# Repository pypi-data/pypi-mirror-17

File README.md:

# PyPI code 17

This repo contains 40000 packages uploaded to PyPI between 
2016-08-28 20:14 and 2016-10-24 17:08.

The repo is 99% (39960/40000) complete.

Package contents can be found [in the code branch](https://github.com/pypi-data/pypi-mirror-17/tree/code/packages).

A browsable package list for all repositories [all packages here](https://pypi-data.github.io/website/repositories/pypi-mirror-17).

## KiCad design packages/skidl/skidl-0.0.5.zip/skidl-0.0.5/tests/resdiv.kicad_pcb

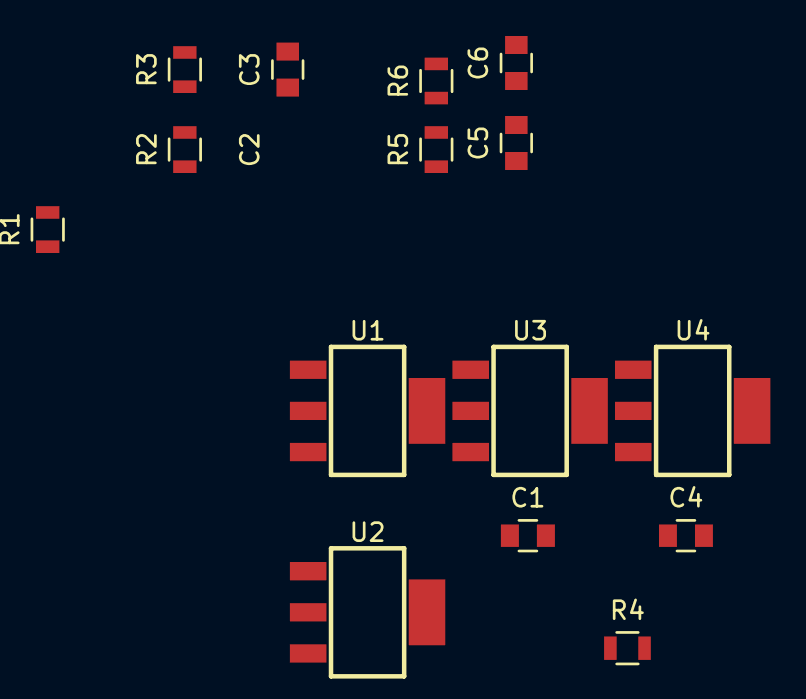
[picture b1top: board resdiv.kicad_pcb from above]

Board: 2 copper layers, 16 parts (0 on the bottom side), 4 nets, no tracks yet.

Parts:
C1, C4: C-NONPOL; C_0805
C2, C5: 1uF; C_0805
C3, C6: 2uF; C_0805
R1, R4: R; R_0805
R2, R5: 1K6; R_0805
R3, R6: 500K3; R_0805
U1, U2, U3, U4: NCV1117; SOT-223

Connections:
A: C2.1, R2.1, U1.3, U2.3
B: C2.2, C3.1, C5.1, R2.2, R3.1, R5.1, U1.2, U2.2, U3.3, U4.3
GND: C3.2, C6.2, R3.2, R6.2, U1.1, U2.1, U3.1, U4.1
unnamed: C5.2, C6.1, R5.2, R6.1, U3.2, U4.2

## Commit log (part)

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2023-08-06 Add package django-fobi/0.9.2/django-fobi-0.9.2.tar.gz
2023-08-06 Add package itchat/1.1.18/itchat-1.1.18-py2.py3-none-any.whl
2023-08-06 Add package ase/3.12.0/ase-3.12.0.tar.gz
2023-08-06 Add package klue-client-server/0.0.102/klue-client-server-0.0.102.tar.gz
2023-08-06 Add package nyaa-cli/0.0.1.dev10/nyaa-cli-0.0.1.dev10.tar.gz
2023-08-06 Add package learn2map/0.2.1/learn2map-0.2.1-py3-none-any.whl
2023-08-06 Add package log4mongo/1.6.0/log4mongo-1.6.0.tar.gz
2023-08-06 Add package zeep/0.20.0/zeep-0.20.0-py2.py3-none-any.whl
2023-08-06 Add package django-wordpress-api/0.1.11/django-wordpress-api-0.1.11.tar.gz
2023-08-06 Add package itchat/1.1.18/itchat-1.1.18.tar.gz
2023-08-06 Add package zeep/0.20.0/zeep-0.20.0.tar.gz
2023-08-06 Add package webm/0.10.0/webm-0.10.0.tar.gz
2023-08-06 Add package HRlo/0.7.2/HRlo-0.7.2.tar.gz
2023-08-06 Add package minicache/0.0.1/minicache-0.0.1.zip
2023-08-06 Add package silent-auction/0.1.3/silent-auction-0.1.3.tar.gz
2023-08-06 Add package invenio-search/1.0.0a8/invenio-search-1.0.0a8.tar.gz
2023-08-06 Add package CryDeer/0.2.3/CryDeer-0.2.3.tar.gz
2023-08-06 Add package uh/0.0.0/uh-0.0.0.tar.gz
2023-08-06 Add package mssqlcli/1.0.1b0/mssqlcli-1.0.1b0.tar.gz
2023-08-06 Add package coin/0.23/coin-0.23.tar.gz
2023-08-06 Add package podaacpy/1.5.0/podaacpy-1.5.0-py3.3.egg
2023-08-06 Add package aloe/0.1.11/aloe-0.1.11.tar.gz
2023-08-06 Add package pyboto3/1.3/pyboto3-1.3-py2.7.egg
2023-08-06 Add package podaacpy/1.5.0/podaacpy-1.5.0.tar.gz
2023-08-06 Add package phrasemachine/1.0.1/phrasemachine-1.0.1.tar.gz
2023-08-06 Add package mamonsu/2.1.3/mamonsu-2.1.3.tar.gz
2023-08-06 Add package wikitextparser/0.8.6.dev1/wikitextparser-0.8.6.dev1.tar.gz
2023-08-06 Add package grako/3.16.2/grako-3.16.2.zip
2023-08-06 Add package pyboto3/1.3/pyboto3-1.3.win32.zip
2023-08-06 Add package plonetheme.blueberry/1.5.3/plonetheme.blueberry-1.5.3.tar.gz
2023-08-06 Add package django-ldapdb/0.7.0/django-ldapdb-0.7.0.tar.gz
2023-08-06 Add package grako/3.16.2/grako-3.16.2.tar.gz
2023-08-06 Add package wikitextparser/0.8.6.dev1/wikitextparser-0.8.6.dev1-py3-none-any.whl
2023-08-06 Add package pyolite/1.4.0/pyolite-1.4.0.tar.gz
2023-08-06 Add package pyboto3/1.3/pyboto3-1.3.tar.gz
2023-08-06 Add package flarecast-service/0.1.0.139/flarecast_service-0.1.0.139-py2-none-any.whl
2023-08-06 Add package flarecast-service/0.1.0.139/flarecast-service-0.1.0.139.tar.gz
2023-08-06 Add package pocsuite/2.0.4.2/pocsuite-2.0.4.2.tar.bz2
2023-08-06 Add package python-unshare/0.2/python-unshare-0.2.tar.gz
2023-08-06 Add package scriptabit/1.12.1/scriptabit-1.12.1.tar.gz
2023-08-06 Add package pocsuite/2.0.4.1/pocsuite-2.0.4.2.tar.gz
2023-08-06 Add package hisparc-sapphire/0.9.31/hisparc_sapphire-0.9.31-py2.7.egg
2023-08-06 Add package proso-apps/3.9.2/proso-apps-3.9.2.tar.gz
2023-08-06 Add package homeassistant/0.31.1/homeassistant-0.31.1.tar.gz
2023-08-06 Add package mycli/1.8.1/mycli-1.8.1-py2.py3-none-any.whl
2023-08-06 Add package pyquant-ms/0.1.43rc1/pyquant_ms-0.1.43rc1-cp27-cp27m-win_amd64.whl
2023-08-06 Add package pyquant-ms/0.1.43rc1/pyquant_ms-0.1.43rc1-cp34-cp34m-win_amd64.whl
2023-08-06 Add package emzed/2.29.2/emzed-2.29.2.zip
2023-08-06 Add package cobra/0.5.3.post3/cobra-0.5.3.post3-cp27-cp27mu-manylinux1_x86_64.whl
2023-08-06 Add package hlsorigin/0.0.7/hlsorigin-0.0.7.tar.gz
2023-08-06 Add package spglib/1.9.7.9/spglib-1.9.7.9-py2.7-linux-x86_64.egg
2023-08-06 Add package cobra/0.5.3/cobra-0.5.3-cp27-cp27m-win32.whl
2023-08-06 Add package spglib/1.9.7.9/spglib-1.9.7.9-py3.5-linux-x86_64.egg
2023-08-06 Add package cobra/0.5.3.post3/cobra-0.5.3.post3-cp33-cp33m-manylinux1_x86_64.whl
2023-08-06 Add package twapi-users/1.2a1/twapi_users-1.2a1.tar.gz
2023-08-06 Add package nesterYLXQ/1.0.0/nesterYLXQ-1.0.0.zip
2023-08-06 Add package sUTL/1.0.5b1/sUTL-1.0.5b1-py2.py3-none-any.whl
2023-08-06 Add package edgy.project/0.1.17/edgy.project-0.1.17-py2.py3-none-any.whl
2023-08-06 Add package BigRLab/1.1.4/BigRLab-1.1.4.zip
2023-08-06 Add package BigRLab/1.1.3/BigRLab-1.1.3.zip
2023-08-06 Add package nesterless/2.0.0/nesterless-2.0.0.zip
2023-08-06 Add package pyquant-ms/0.1.43rc1/pyquant_ms-0.1.43rc1-cp35-cp35m-win_amd64.whl
2023-08-06 Add package cobra/0.5.3/cobra-0.5.3-cp35-cp35m-win32.whl
2023-08-06 Add package cgen/2016.2.1/cgen-2016.2.1.tar.gz
2023-08-06 Add package cobra/0.5.3/cobra-0.5.3-cp34-cp34m-win_amd64.whl
2023-08-06 Add package cobra/0.5.3/cobra-0.5.3-cp35-cp35m-win_amd64.whl
2023-08-06 Add package component_builder/1.0.1.53/component_builder-1.0.1.53.tar.gz
2023-08-06 Add package LI-AWS-Deploy/1.3.4/LI_AWS_Deploy-1.3.4-py2-none-any.whl
2023-08-06 Add package edgy.project/0.1.17/edgy.project-0.1.17-py3.5.egg
2023-08-06 Add package edgy.project/0.1.17/edgy.project-0.1.17.macosx-10.12-x86_64.tar.gz
2023-08-06 Add package edgy.project/0.1.17/edgy.project-0.1.17.tar.gz
2023-08-06 Add package pyquant-ms/0.1.43rc1/pyquant_ms-0.1.43rc1-cp35-cp35m-win32.whl
2023-08-06 Add package learn2map/0.2.2/learn2map-0.2.2.tar.gz
2023-08-06 Add package docker-hub/0.0.4/docker_hub-0.0.4-py2.py3-none-any.whl
2023-08-06 Add package sentry-irc/3.2.0/sentry-irc-3.2.0.tar.gz
2023-08-06 Add package onegov.user/0.8.1/onegov.user-0.8.1.tar.gz
2023-08-06 Add package onegov.user/0.8.1/onegov.user-0.8.1-py3-none-any.whl
2023-08-06 Add package BigRLab_algo_mgr/1.1.1/BigRLab_algo_mgr-1.1.1.zip
2023-08-06 Add package mamonsu/2.1.1/mamonsu-2.1.1.tar.gz
2023-08-06 Add package nesterYLXQ/1.2.0/nesterYLXQ-1.2.0.zip
2023-08-06 Add package TypeCastSimple/1.0.0/TypeCastSimple-1.0.0.zip
2023-08-06 Add package django-reversion-compare/0.7.2/django-reversion-compare-0.7.2.tar.gz
2023-08-06 Add package collections-extended/0.8.2/collections-extended-0.8.2.tar.gz
2023-08-06 Add package lswapi/0.3.0/lswapi-0.3.0.tar.gz
2023-08-06 Add package LI-AWS-Deploy/1.3.4/LI-AWS-Deploy-1.3.4.tar.gz
2023-08-06 Add package BigRLab_algo_mgr/1.1.0/BigRLab_algo_mgr-1.1.0.zip
2023-08-06 Add package cobra/0.5.4/cobra-0.5.4-cp27-cp27m-manylinux1_x86_64.whl
2023-08-06 Add package basescript/0.1.2/basescript-0.1.2-py2-none-any.whl
2023-08-06 Add package funcserver/0.2.7/funcserver-0.2.7.tar.gz
2023-08-06 Add package cobra/0.5.4/cobra-0.5.4-cp27-cp27m-win32.whl
2023-08-06 Add package cobra/0.5.4/cobra-0.5.4-cp34-cp34m-win32.whl
2023-08-06 Add package jenkins-epo/1.63/jenkins-epo-1.63.tar.gz
2023-08-06 Add package cobra/0.5.4/cobra-0.5.4-cp34-cp34m-win_amd64.whl
2023-08-06 Add package mamonsu/2.1.2/mamonsu-2.1.2.tar.gz
2023-08-06 Add package kotti_theme_sbadmin/0.1.0/kotti_theme_sbadmin-0.1.0.tar.gz
2023-08-06 Add package cobra/0.5.4/cobra-0.5.4-cp35-cp35m-win32.whl
2023-08-06 Add package tap2junit/0.0.2/tap2junit-0.0.2.tar.gz
2023-08-06 Add package hexgrid-py/1.0/hexgrid-py-1.0.tar.gz
2023-08-06 Add package chris_nester/0.0.0/chris_nester-0.0.0.tar.gz
2023-08-06 Add package Flask-SQLAlchemy-Booster/0.4.43/Flask-SQLAlchemy-Booster-0.4.43.tar.gz
2023-08-06 Add package fnapy/1.1.2/fnapy-1.1.2-py2.py3-none-any.whl
2023-08-06 Add package morton-py/1.0/morton-py-1.0.tar.gz
2023-08-06 Add package tap2junit/0.0.3/tap2junit-0.0.3.tar.gz
2023-08-06 Add package jenkins-epo/1.64/jenkins-epo-1.64.tar.gz
2023-08-06 Add package statik/0.7.0/statik-0.7.0.tar.gz
2023-08-06 Add package tap2junit/0.0.5/tap2junit-0.0.5.tar.gz
2023-08-06 Add package pyquant-ms/0.1.43rc2/pyquant_ms-0.1.43rc2-cp35-cp35m-win_amd64.whl
2023-08-06 Add package cornice/2.0.1/cornice-2.0.1-py2.py3-none-any.whl
2023-08-06 Add package jenkins-epo/1.64/jenkins_epo-1.64-py3-none-any.whl
2023-08-06 Add package chris_nester/1.2.0/chris_nester-1.2.0.tar.gz
2023-08-06 Add package quality-report/1.65.1/quality_report-1.65.1.tar.gz
2023-08-06 Add package odl/0.5.1/odl-0.5.1.tar.gz
2023-08-06 Add package wakatime/6.2.0/wakatime-6.2.0.tar.gz
2023-08-06 Add package cubicweb-saem-ref/0.13.0/cubicweb-saem-ref-0.13.0.tar.gz
2023-08-06 Add package tap2junit/0.1.0/tap2junit-0.1.0.tar.gz
2023-08-06 Add package docker-netowrk-capture/0.6.0/docker-netowrk-capture-0.6.0.tar.gz
2023-08-06 Add package pyfcm/1.0.8/pyfcm-1.0.8-py2-none-any.whl
2023-08-06 Add package galaxy-lib/16.10.10/galaxy_lib-16.10.10-py2.7.egg
2023-08-06 Add package pyquant-ms/0.1.43rc2/pyquant_ms-0.1.43rc2-cp35-cp35m-win32.whl
2023-08-06 Add package django-sane-redirects/1.0.2/django-sane-redirects-1.0.2.tar.gz
2023-08-06 Add package qutils/0.2/qutils-0.2.tar.gz
2023-08-06 Add package chris_nester/1.3.0/chris_nester-1.3.0.tar.gz
2023-08-06 Add package tomacco/0.4.4/tomacco-0.4.4.tar.gz
2023-08-06 Add package django-localized-fields/1.5/django-localized-fields-1.5.tar.gz
2023-08-06 Add package slurm-pipeline/1.0.5/slurm-pipeline-1.0.5.tar.gz
2023-08-06 Add package tipsi-tools/0.14.1/tipsi_tools-0.14.1.tar.gz
2023-08-06 Add package Flask-SQLAlchemy-Booster/0.4.44/Flask-SQLAlchemy-Booster-0.4.44.tar.gz
2023-08-06 Add package transientNamer/0.1.6/transientNamer-0.1.6.tar.gz
2023-08-06 Add package i18nize/0.0.2/i18nize-0.0.2.tar.gz
2023-08-06 Add package wikitextparser/0.8.5.dev1/wikitextparser-0.8.5.dev1-py3-none-any.whl
2023-08-06 Add package mamonsu/2.1.4/mamonsu-2.1.4.tar.gz
2023-08-06 Add package pytest-warnings/0.2.0/pytest-warnings-0.2.0.zip
2023-08-06 Add package Heatshrink/0.2.4/Heatshrink-0.2.4.tar.gz
2023-08-06 Add package pytablewriter/0.11.1/pytablewriter-0.11.1.tar.gz
2023-08-06 Add package sphinx-boost/0.0.2/sphinx-boost-0.0.2.tar.gz
2023-08-06 Add package tenacity/3.3.0/tenacity-3.3.0.tar.gz
2023-08-06 Add package conda-mirror/0.0.2/conda_mirror-0.0.2.tar.gz
2023-08-06 Add package google-i18n-address/2.0.0/google-i18n-address-2.0.0.tar.gz
2023-08-06 Add package fundamentals/0.8.7/fundamentals-0.8.7.tar.gz
2023-08-06 Add package django-painless-seo/0.0.9/django-painless-seo-0.0.9.tar.gz
2023-08-06 Add package cdo/1.3.2/cdo-1.3.2.tar.gz
2023-08-06 Add package bob.pad.base/1.0.5/bob.pad.base-1.0.5.zip
2023-08-06 Add package pytablereader/0.1.1/pytablereader-0.1.1.tar.gz
2023-08-06 Add package infoblox-client/0.4.9.post1/infoblox_client-0.4.9.post1-py2.py3-none-any.whl
2023-08-06 Add package pytablereader/0.1.1/pytablereader-0.1.1-py2.py3-none-any.whl
2023-08-06 Add package PyPika/0.1.0/PyPika-0.1.0.tar.gz
2023-08-06 Add package django-enum-field/0.1/django_enum_field-0.1-py2-none-any.whl
2023-08-06 Add package stoq/1.12.0rc1.post1/stoq-1.12.0rc1.post1.tar.gz
2023-08-06 Add package tap2junit/0.1.1/tap2junit-0.1.1.tar.gz
2023-08-06 Add package ftw.upgrade/2.0.5/ftw.upgrade-2.0.5.tar.gz
2023-08-06 Add package django-enum-field/0.1/django-enum-field-0.1.tar.gz
2023-08-06 Add package pycdstar/0.3.0/pycdstar-0.3.0.tar.gz
2023-08-06 Add package coala-bears/0.9.0.dev20161024154657/coala_bears-0.9.0.dev20161024154657-py3-none-any.whl
2023-08-06 Add package vesna-spectrumsensor/1.0.5/vesna-spectrumsensor-1.0.5.tar.gz
2023-08-06 Add package fundamentals/0.8.8/fundamentals-0.8.8.tar.gz
2023-08-06 Add package aws-vapor/0.0.12/aws-vapor-0.0.12.tar.gz
2023-08-06 Add package django-concepts/0.7.1/django_concepts-0.7.1-py2-none-any.whl
2023-08-06 Add package loompy/0.20.0/loompy-0.20.0.tar.gz
2023-08-06 Add package loompy/0.20.3/loompy-0.20.3.tar.gz
2023-08-06 Add package pydradis/0.1/pydradis-0.1.tar.gz
2023-08-06 Add package django-msp-sms/1.3.0/django_msp_sms-1.3.0.zip
2023-08-06 Add package arco_nester/1.1.0/arco_nester-1.1.0.tar.gz
2023-08-06 Add package aiocache/0.1.0/aiocache-0.1.0.tar.gz
2023-08-06 Add package smappy/0.2.8/smappy-0.2.8.tar.gz
2023-08-06 Add package smappy/0.2.8/smappy-0.2.8-py3-none-any.whl
2023-08-06 Add package apitopy/0.4.0/apitopy-0.4.0.tar.gz
2023-08-06 Add package loompy/0.20.4/loompy-0.20.4.tar.gz
2023-08-06 Add package tiros/1.0.4/tiros-1.0.4-py2.py3-none-any.whl
2023-08-06 Add package sphinx-boost/0.0.3/sphinx-boost-0.0.3.tar.gz
2023-08-06 Add package apitopy/0.4.0/apitopy-0.4.0-py2-none-any.whl
2023-08-06 Add package django-msp-sms/1.4.0/django_msp_sms-1.4.0.zip
2023-08-06 Add package humann2/0.9.5/humann2-0.9.5.tar.gz
2023-08-06 Add package pixiedust-flightpredict/0.5/pixiedust_flightpredict-0.5.tar.gz
